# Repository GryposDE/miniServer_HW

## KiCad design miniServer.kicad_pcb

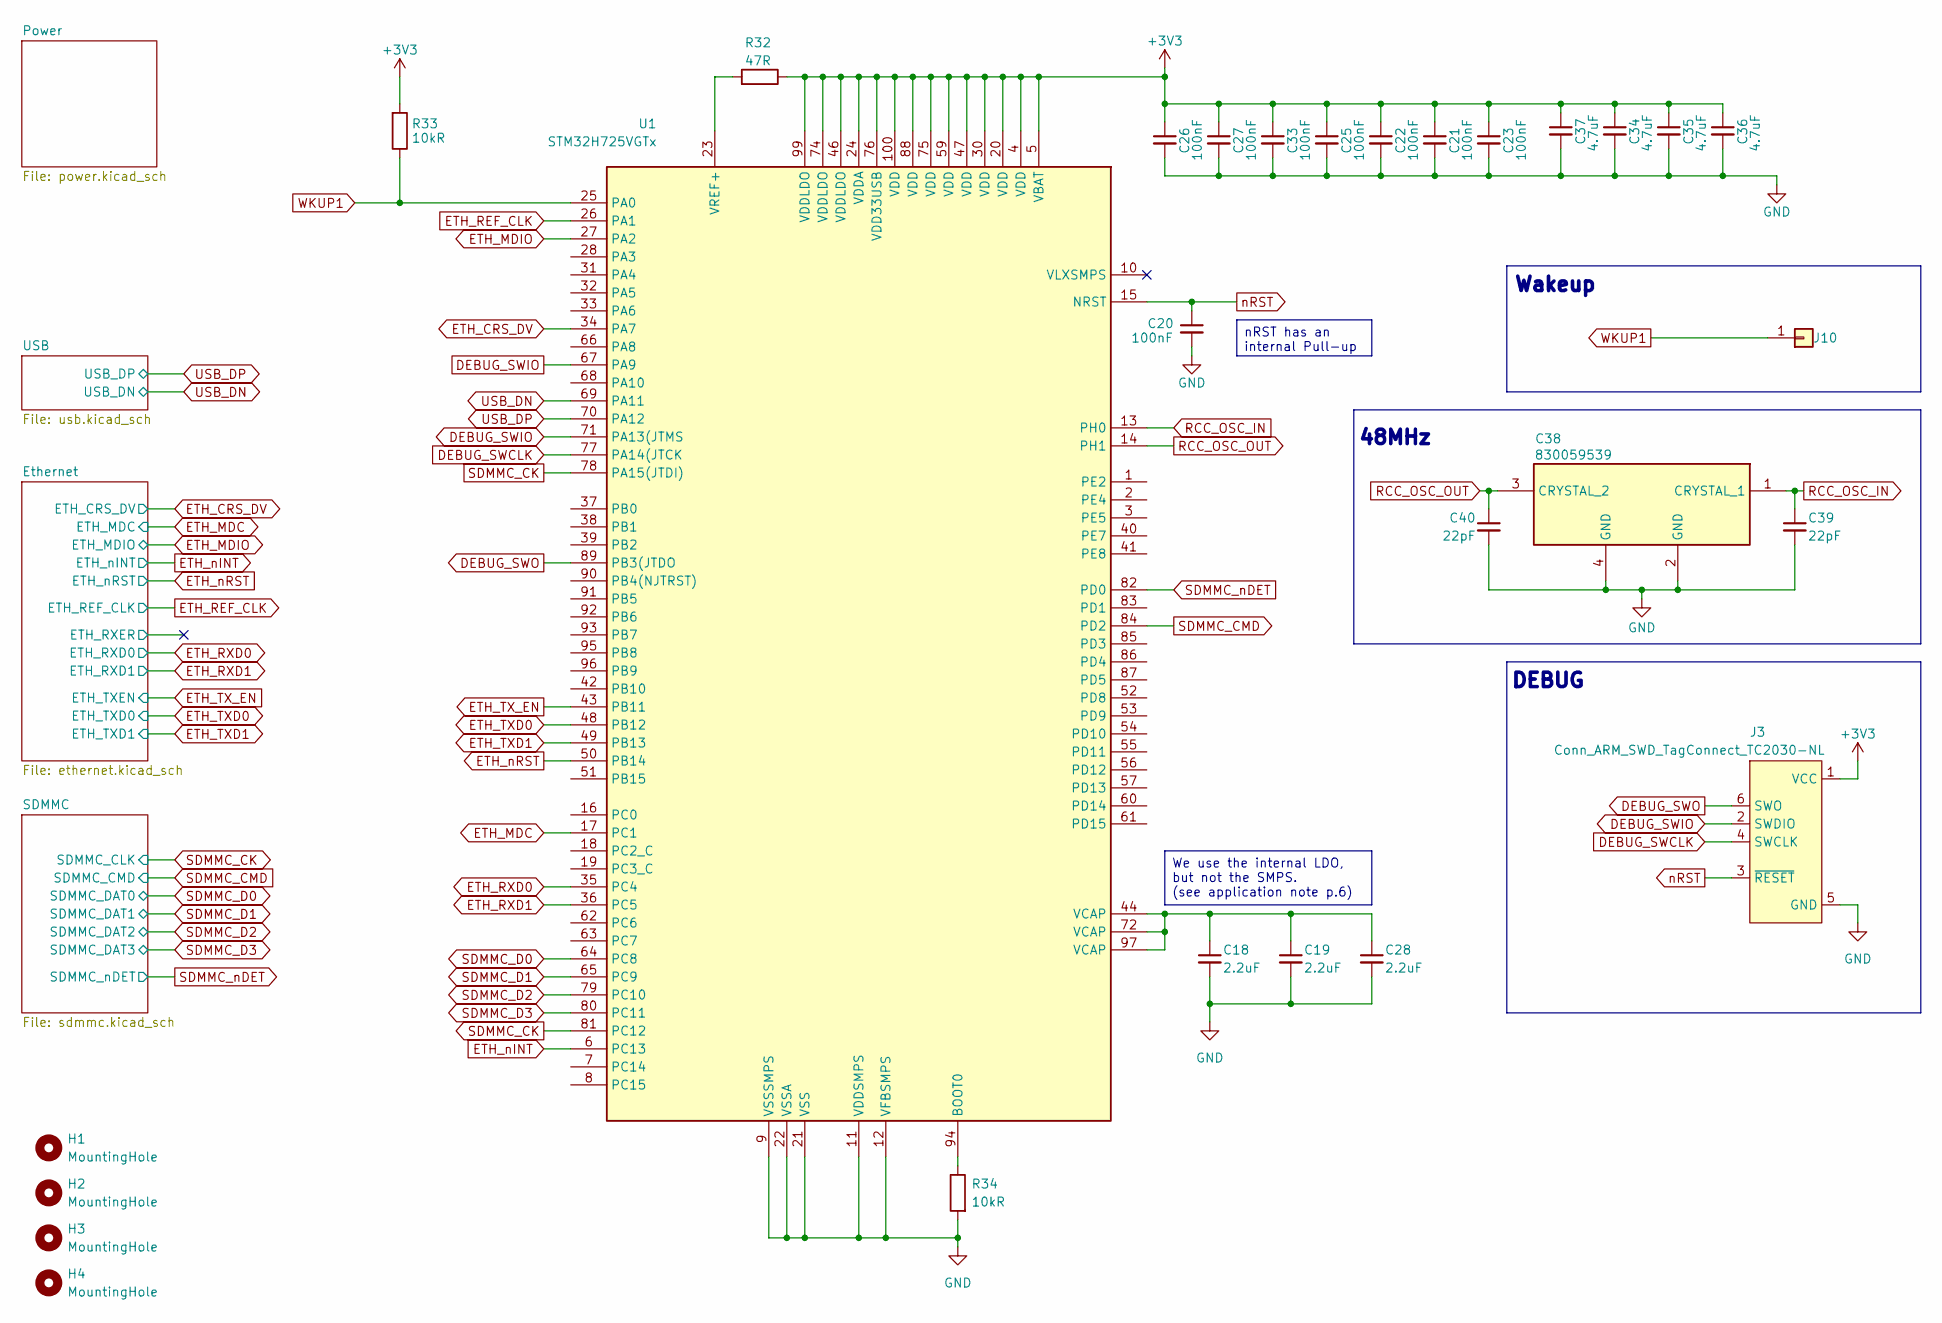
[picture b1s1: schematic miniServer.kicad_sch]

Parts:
C18, C19, C28: 2.2uF; C_0805_2012Metric_Pad1.18x1.45mm_HandSolder
C20, C21, C22, C23, C25, C26, C27, C33: 100nF; C_0805_2012Metric_Pad1.18x1.45mm_HandSolder
C34, C35, C36, C37: 4.7uF; C_0805_2012Metric_Pad1.18x1.45mm_HandSolder
C38: 830059539; Mouser Part Number 710-830059539
C39, C40: 22pF; C_0805_2012Metric_Pad1.18x1.45mm_HandSolder
H1, H2, H3, H4: MountingHole; MountingHole_2.2mm_M2
J3: Conn_ARM_SWD_TagConnect_TC2030-NL; Tag-Connect_TC2030-IDC-NL_2x03_P1.27mm_Vertical
J10: Conn_01x01; SolderWirePad_1x01_SMD_1.5x3mm
R32: 47R; R_0805_2012Metric_Pad1.20x1.40mm_HandSolder
R33, R34: 10kR; R_0805_2012Metric_Pad1.20x1.40mm_HandSolder
U1: STM32H725VGTx; LQFP-100_14x14mm_P0.5mm

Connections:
+3V3: C21.1, C22.1, C23.1, C25.1, C26.1, C27.1, C33.1, C34.1, C35.1, C36.1, C37.1, J3.1 (VCC), R32.1, R33.2, U1.4 (VDD), U1.5 (VBAT), U1.20 (VDD), U1.24 (VDDA), U1.30 (VDD), U1.46 (VDDLDO), U1.47 (VDD), U1.59 (VDD), U1.74 (VDDLDO), U1.75 (VDD), U1.76 (VDD33USB), U1.88 (VDD), U1.99 (VDDLDO), U1.100 (VDD); also elsewhere on the board
DEBUG_SWCLK: J3.4 (SWCLK), U1.77 (PA14(JTCK)
DEBUG_SWIO: J3.2 (SWDIO), U1.67 (PA9), U1.71 (PA13(JTMS)
DEBUG_SWO: J3.6 (SWO), U1.89 (PB3(JTDO)
ETH_CRS_DV: U1.34 (PA7); also elsewhere on the board
ETH_MDC: U1.17 (PC1); also elsewhere on the board
ETH_MDIO: U1.27 (PA2); also elsewhere on the board
ETH_REF_CLK: U1.26 (PA1); also elsewhere on the board
ETH_RXD0: U1.35 (PC4); also elsewhere on the board
ETH_RXD1: U1.36 (PC5); also elsewhere on the board
ETH_TXD0: U1.48 (PB12); also elsewhere on the board
ETH_TXD1: U1.49 (PB13); also elsewhere on the board
ETH_TX_EN: U1.43 (PB11); also elsewhere on the board
ETH_nINT: U1.6 (PC13); also elsewhere on the board
ETH_nRST: U1.50 (PB14); also elsewhere on the board
GND: C18.2, C19.2, C20.2, C21.2, C22.2, C23.2, C25.2, C26.2, C27.2, C28.2, C33.2, C34.2, C35.2, C36.2, C37.2, C38.2 (GND), C38.4 (GND), C39.2, C40.2, J3.5 (GND), R34.2, U1.9 (VSSSMPS), U1.11 (VDDSMPS), U1.12 (VFBSMPS), U1.21 (VSS), U1.22 (VSSA), U1.29 (VSS), U1.45 (VSS), U1.58 (VSS), U1.73 (VSS), U1.98 (VSS); also elsewhere on the board
unnamed: C18.1, C19.1, C28.1, U1.44 (VCAP), U1.72 (VCAP), U1.97 (VCAP)
unnamed: R34.1, U1.94 (BOOT0)
unnamed: R32.2, U1.23 (VREF+)
RCC_OSC_IN: C38.1 (CRYSTAL_1), C39.1, U1.13 (PH0)
RCC_OSC_OUT: C38.3 (CRYSTAL_2), C40.1, U1.14 (PH1)
SDMMC_CK: U1.78 (PA15(JTDI)), U1.81 (PC12); also elsewhere on the board
SDMMC_CMD: U1.84 (PD2); also elsewhere on the board
SDMMC_D0: U1.64 (PC8); also elsewhere on the board
SDMMC_D1: U1.65 (PC9); also elsewhere on the board
SDMMC_D2: U1.79 (PC10); also elsewhere on the board
SDMMC_D3: U1.80 (PC11); also elsewhere on the board
SDMMC_nDET: U1.82 (PD0); also elsewhere on the board
USB_DN: U1.69 (PA11); also elsewhere on the board
USB_DP: U1.70 (PA12); also elsewhere on the board
WKUP1: J10.1, R33.1, U1.25 (PA0)
nRST: C20.1, J3.3 (~RESET), U1.15 (NRST)

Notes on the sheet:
DEBUG
48MHz
Wakeup
nRST has an internal Pull-up
We use the internal LDO, but not the SMPS. (see application note p.6)

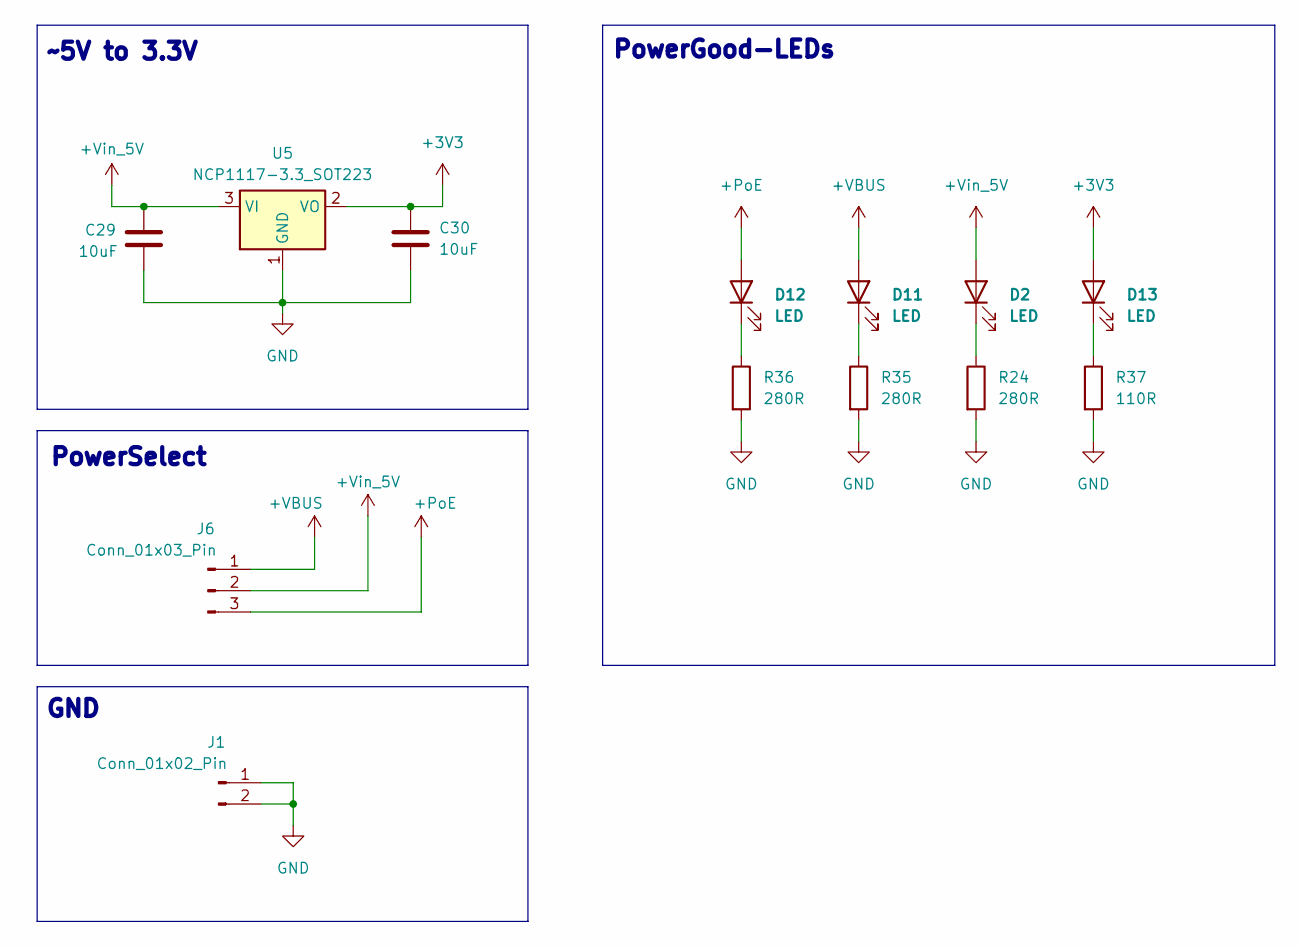
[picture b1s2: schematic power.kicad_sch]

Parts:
C29, C30: 10uF; C_0805_2012Metric_Pad1.18x1.45mm_HandSolder
D2, D11, D12, D13: LED; LED_0805_2012Metric_Pad1.15x1.40mm_HandSolder
J1: Conn_01x02_Pin; SolderWire-0.15sqmm_1x02_P4mm_D0.5mm_OD1.5mm
J6: Conn_01x03_Pin; SolderWire-0.15sqmm_1x03_P4mm_D0.5mm_OD1.5mm
R24, R35, R36: 280R; R_0805_2012Metric_Pad1.20x1.40mm_HandSolder
R37: 110R; R_0805_2012Metric_Pad1.20x1.40mm_HandSolder
U5: NCP1117-3.3_SOT223; SOT-223-3_TabPin2

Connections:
+3V3: C30.1, D13.2 (A), U5.2 (VO); also elsewhere on the board
+PoE: D12.2 (A), J6.3; also elsewhere on the board
+VBUS: D11.2 (A), J6.1; also elsewhere on the board
+Vin_5V: C29.1, D2.2 (A), J6.2, U5.3 (VI)
GND: C29.2, C30.2, J1.1, J1.2, R24.2, R35.2, R36.2, R37.2, U5.1 (GND); also elsewhere on the board
unnamed: D2.1 (K), R24.1
unnamed: D11.1 (K), R35.1
unnamed: D12.1 (K), R36.1
unnamed: D13.1 (K), R37.1

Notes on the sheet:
~5V to 3.3V
PowerSelect
PowerGood-LEDs
GND

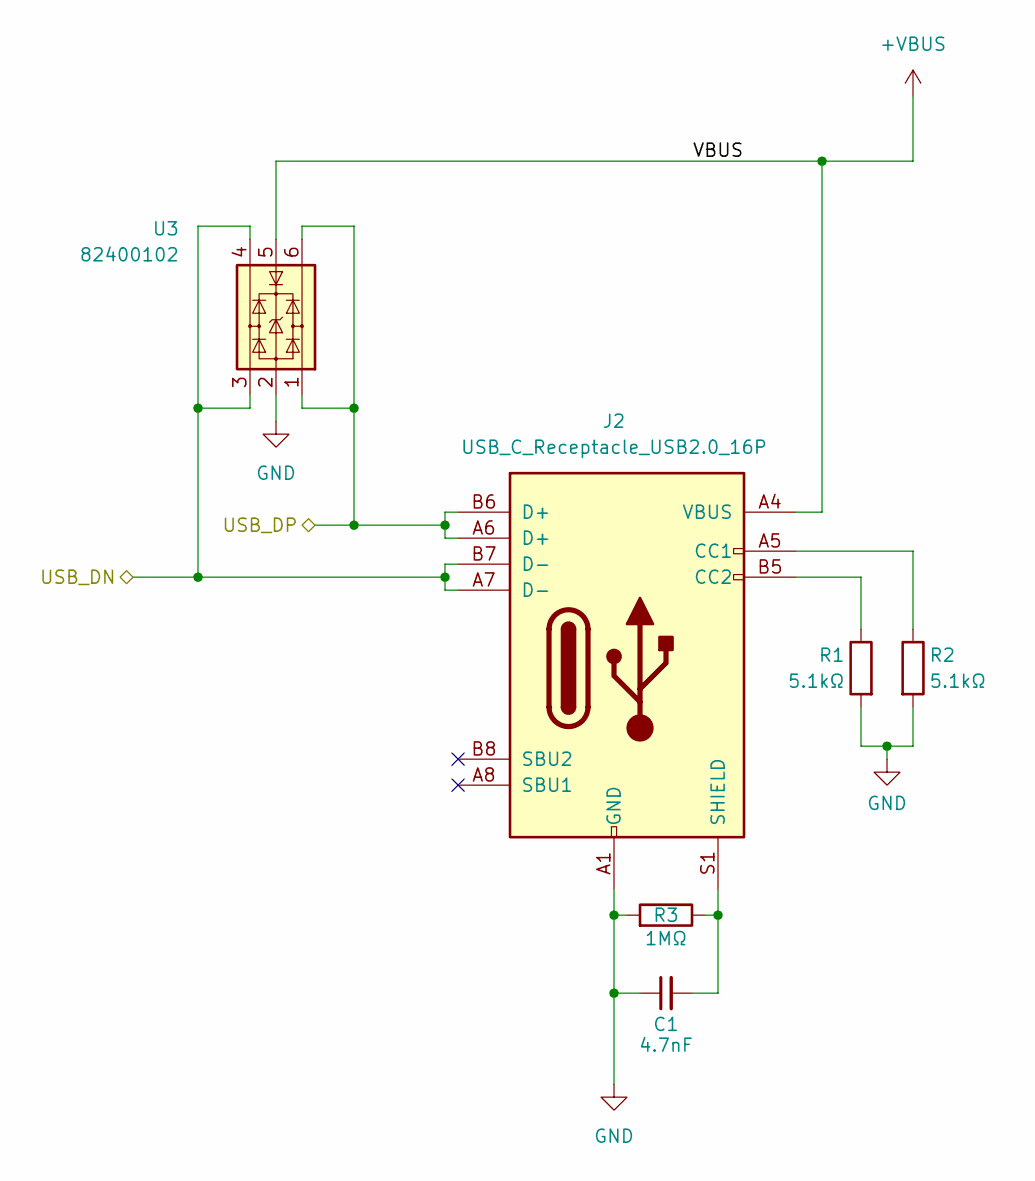
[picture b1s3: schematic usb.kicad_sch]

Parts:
C1: 4.7nF; C_0805_2012Metric_Pad1.18x1.45mm_HandSolder
J2: USB_C_Receptacle_USB2.0_16P; USB_C_Receptacle_GCT_USB4105-xx-A_16P_TopMnt_Horizontal
R1, R2: 5.1kΩ; R_0805_2012Metric_Pad1.20x1.40mm_HandSolder
R3: 1MΩ; R_0805_2012Metric_Pad1.20x1.40mm_HandSolder
U3: 82400102; SOT-23-6

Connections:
+VBUS: J2.A4 (VBUS), J2.A9 (VBUS), J2.B4 (VBUS), J2.B9 (VBUS), U3.5; also elsewhere on the board
GND: C1.1, J2.A1 (GND), J2.A12 (GND), J2.B1 (GND), J2.B12 (GND), R1.2, R2.2, R3.2, U3.2; also elsewhere on the board
unnamed: J2.A5 (CC1), R2.1
unnamed: J2.B5 (CC2), R1.1
unnamed: C1.2, J2.S1 (SHIELD), R3.1
USB_DN: J2.A7 (D-), J2.B7 (D-), U3.3, U3.4; also elsewhere on the board
USB_DP: J2.A6 (D+), J2.B6 (D+), U3.1, U3.6; also elsewhere on the board

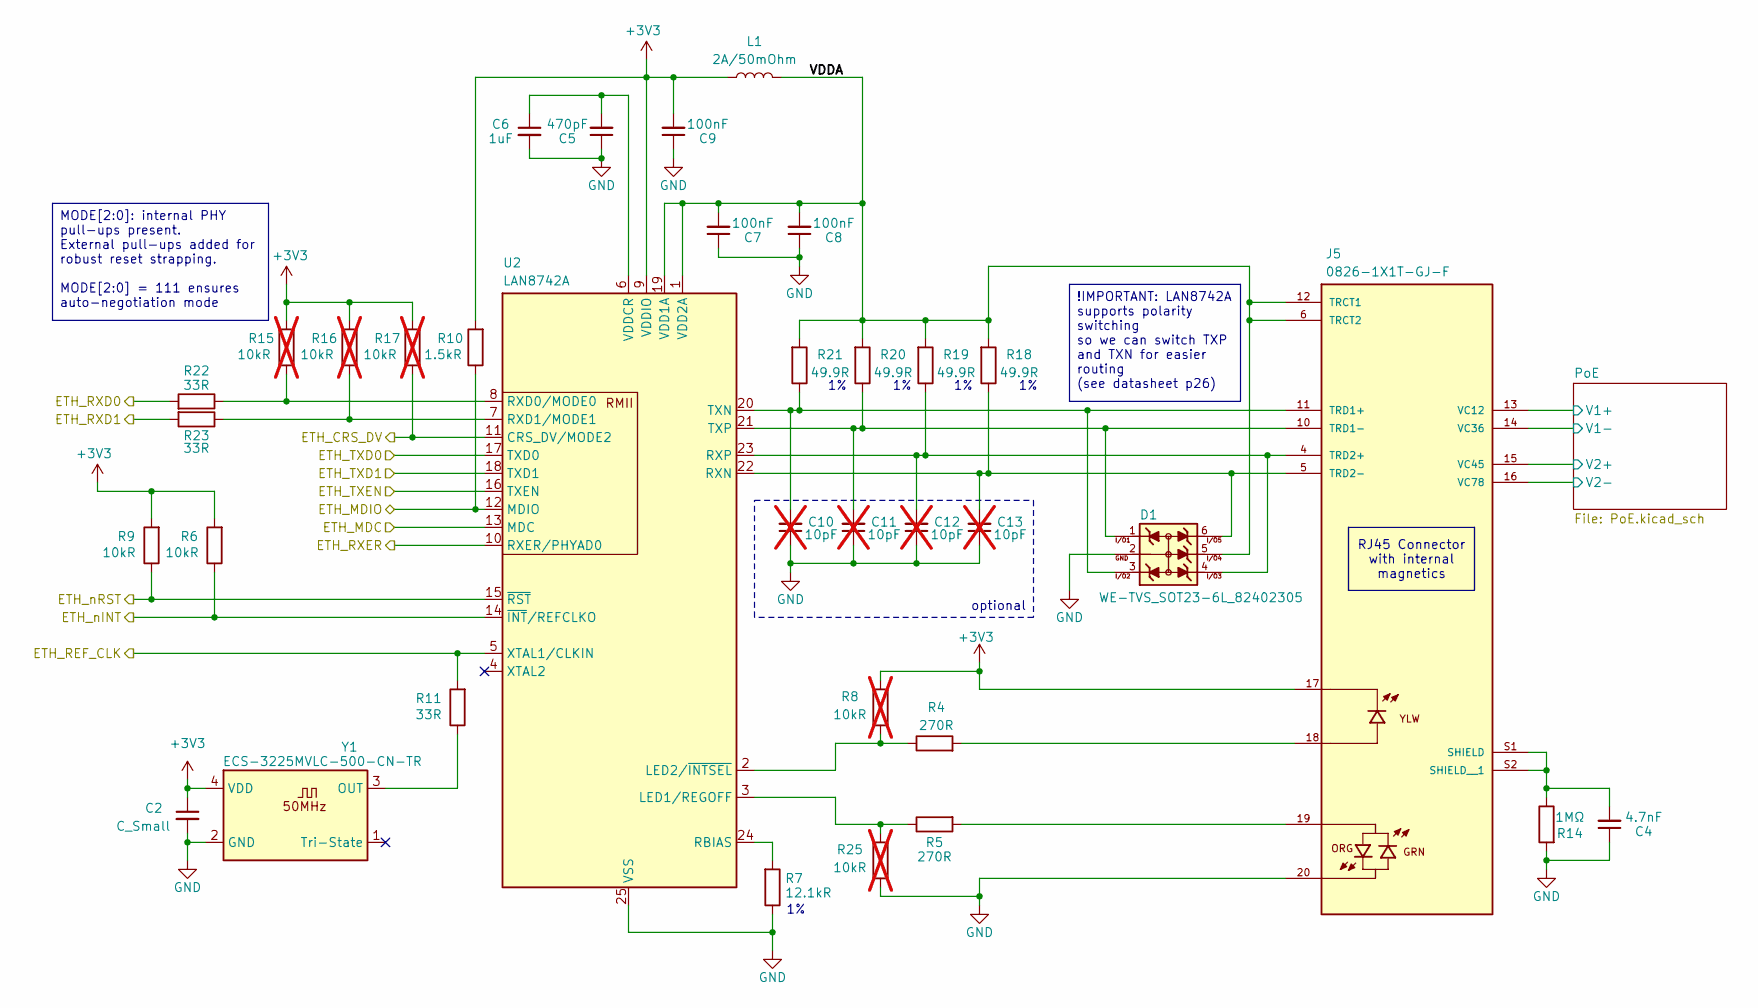
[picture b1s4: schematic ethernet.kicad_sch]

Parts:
C2: C_Small; C_0805_2012Metric_Pad1.18x1.45mm_HandSolder
C4: 4.7nF; C_0805_2012Metric_Pad1.18x1.45mm_HandSolder
C5: 470pF; C_0805_2012Metric_Pad1.18x1.45mm_HandSolder
C6: 1uF; C_0805_2012Metric_Pad1.18x1.45mm_HandSolder
C7, C8, C9: 100nF; C_0805_2012Metric_Pad1.18x1.45mm_HandSolder
C10, C11, C12, C13: 10pF; C_0805_2012Metric_Pad1.18x1.45mm_HandSolder; not fitted
D1: WE-TVS_SOT23-6L_82402305; WE-TVS_SOT23-6L
J5: 0826-1X1T-GJ-F; BEL_0826-1X1T-GJ-F; PARTREV D
L1: 2A/50mOhm; L_0805_2012Metric_Pad1.05x1.20mm_HandSolder
R4, R5: 270R; R_0805_2012Metric_Pad1.20x1.40mm_HandSolder
R6, R9: 10kR; R_0805_2012Metric_Pad1.20x1.40mm_HandSolder
R7: 12.1kR; R_0805_2012Metric_Pad1.20x1.40mm_HandSolder
R8, R15, R16, R17, R25: 10kR; R_0805_2012Metric_Pad1.20x1.40mm_HandSolder; not fitted
R10: 1.5kR; R_0805_2012Metric_Pad1.20x1.40mm_HandSolder
R11, R22, R23: 33R; R_0805_2012Metric_Pad1.20x1.40mm_HandSolder
R14: 1MΩ; R_0805_2012Metric_Pad1.20x1.40mm_HandSolder
R18, R19, R20, R21: 49.9R; R_0805_2012Metric_Pad1.20x1.40mm_HandSolder
U2: LAN8742A; VQFN-24-1EP_4x4mm_P0.5mm_EP2.5x2.5mm_ThermalVias
Y1: ECS-3225MVLC-500-CN-TR; Oscillator_SMD_ECS_2520MV-xxx-xx-4Pin_2.5x2.0mm

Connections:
+3V3: C2.1, C9.2, J5.17, L1.1, R6.2, R8.2, R9.2, R10.2, R15.2, R16.2, R17.2, U2.9 (VDDIO), Y1.4 (VDD); also elsewhere on the board
/Ethernet/ETH_RXER: U2.10 (RXER/PHYAD0)
/Ethernet/PoE/V1+: J5.13 (VC12); also elsewhere on the board
/Ethernet/PoE/V1-: J5.14 (VC36); also elsewhere on the board
/Ethernet/PoE/V2+: J5.15 (VC45); also elsewhere on the board
/Ethernet/PoE/V2-: J5.16 (VC78); also elsewhere on the board
/Ethernet/VDDA: C7.2, C8.2, D1.5, J5.6 (TRCT2), J5.12 (TRCT1), L1.2, R18.2, R19.2, R20.2, R21.2, U2.1 (VDD2A), U2.19 (VDD1A)
ETH_CRS_DV: R17.1, U2.11 (CRS_DV/MODE2); also elsewhere on the board
ETH_MDC: U2.13 (MDC); also elsewhere on the board
ETH_MDIO: R10.1, U2.12 (MDIO); also elsewhere on the board
ETH_REF_CLK: R11.2, U2.5 (XTAL1/CLKIN); also elsewhere on the board
ETH_RXD0: R22.2; also elsewhere on the board
ETH_RXD1: R23.2; also elsewhere on the board
ETH_TXD0: U2.17 (TXD0); also elsewhere on the board
ETH_TXD1: U2.18 (TXD1); also elsewhere on the board
ETH_TX_EN: U2.16 (TXEN); also elsewhere on the board
ETH_nINT: R6.1, U2.14 (~INT/REFCLKO); also elsewhere on the board
ETH_nRST: R9.1, U2.15 (~RST); also elsewhere on the board
GND: C2.2, C4.1, C5.1, C6.2, C7.1, C8.1, C9.1, C10.1, C11.1, C12.1, C13.1, D1.2, J5.20, R7.1, R14.2, R25.1, U2.25 (VSS), Y1.2 (GND); also elsewhere on the board
unnamed: J5.18, R4.2
unnamed: J5.19, R5.2
unnamed: C4.2, J5.S1 (SHIELD), J5.S2 (SHIELD__1), R14.1
unnamed: C10.2, D1.3, J5.11 (TRD1+), R21.1, U2.20 (TXN)
unnamed: C11.2, D1.1, J5.10 (TRD1-), R20.1, U2.21 (TXP)
unnamed: C12.2, D1.4, J5.4 (TRD2+), R19.1, U2.23 (RXP)
unnamed: C13.2, D1.6, J5.5 (TRD2-), R18.1, U2.22 (RXN)
unnamed: R5.1, R25.2, U2.3 (LED1/REGOFF)
unnamed: R4.1, R8.1, U2.2 (LED2/~INTSEL)
unnamed: R7.2, U2.24 (RBIAS)
unnamed: R15.1, R22.1, U2.8 (RXD0/MODE0)
unnamed: R16.1, R23.1, U2.7 (RXD1/MODE1)
unnamed: C5.2, C6.1, U2.6 (VDDCR)
unnamed: R11.1, Y1.3 (OUT)

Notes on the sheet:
RJ45 Connector with internal magnetics
!IMPORTANT: LAN8742A supports polarity switching so we can switch TXP and TXN for easier routing (see datasheet p26)
MODE[2:0]: internal PHY pull-ups present. External pull-ups added for robust reset strapping. MODE[2:0] = 111 ensures auto-negotiation mode
optional

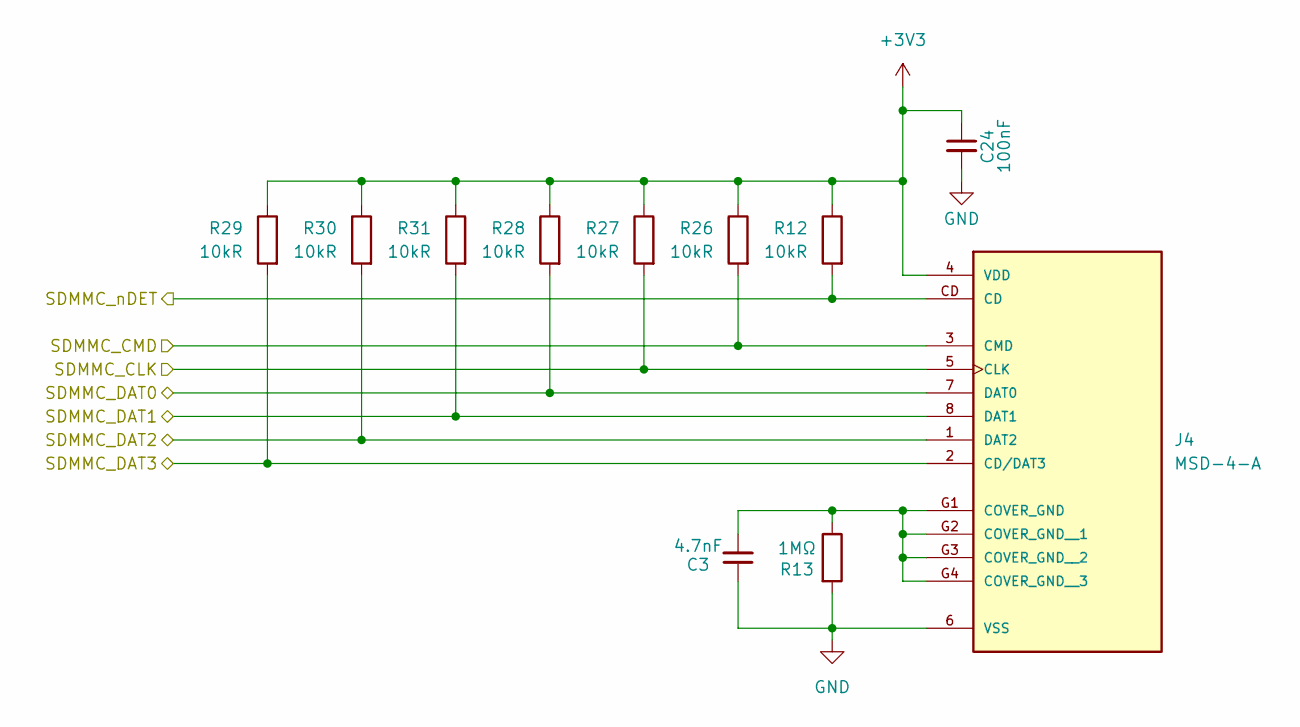
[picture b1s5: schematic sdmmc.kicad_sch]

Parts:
C3: 4.7nF; C_0805_2012Metric_Pad1.18x1.45mm_HandSolder
C24: 100nF; C_0805_2012Metric_Pad1.18x1.45mm_HandSolder
J4: MSD-4-A; CUI_MSD-4-A; PARTREV 1.0
R12, R26, R27, R28, R29, R30, R31: 10kR; R_0805_2012Metric_Pad1.20x1.40mm_HandSolder
R13: 1MΩ; R_0805_2012Metric_Pad1.20x1.40mm_HandSolder

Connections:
+3V3: C24.1, J4.4 (VDD), R12.1, R26.1, R27.1, R28.1, R29.1, R30.1, R31.1; also elsewhere on the board
GND: C3.1, C24.2, J4.6 (VSS), R13.2; also elsewhere on the board
unnamed: C3.2, J4.G1 (COVER_GND), J4.G2 (COVER_GND__1), J4.G3 (COVER_GND__2), J4.G4 (COVER_GND__3), R13.1
SDMMC_CK: J4.5 (CLK), R27.2; also elsewhere on the board
SDMMC_CMD: J4.3 (CMD), R26.2; also elsewhere on the board
SDMMC_D0: J4.7 (DAT0), R28.2; also elsewhere on the board
SDMMC_D1: J4.8 (DAT1), R31.2; also elsewhere on the board
SDMMC_D2: J4.1 (DAT2), R30.2; also elsewhere on the board
SDMMC_D3: J4.2 (CD/DAT3), R29.2; also elsewhere on the board
SDMMC_nDET: J4.CD, R12.2; also elsewhere on the board

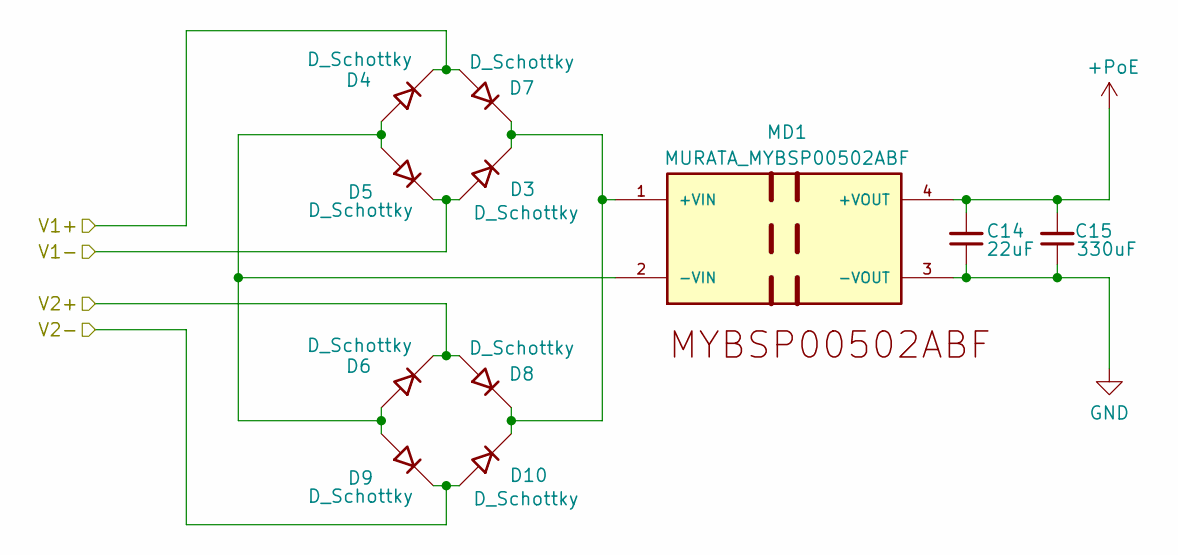
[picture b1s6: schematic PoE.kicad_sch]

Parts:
C14: 22uF; C_0805_2012Metric_Pad1.18x1.45mm_HandSolder
C15: 330uF; C_0805_2012Metric_Pad1.18x1.45mm_HandSolder
D3, D4, D5, D6, D7, D8, D9, D10: D_Schottky; Nexperia_CFP3_SOD-123W
MD1: MURATA_MYBSP00502ABF; MURATA_MYBSP00502ABF_0

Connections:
+PoE: C14.2, C15.2, MD1.4 (+VOUT); also elsewhere on the board
/Ethernet/PoE/V1+: D4.1 (K), D7.2 (A); also elsewhere on the board
/Ethernet/PoE/V1-: D3.2 (A), D5.1 (K); also elsewhere on the board
/Ethernet/PoE/V2+: D6.1 (K), D8.2 (A); also elsewhere on the board
/Ethernet/PoE/V2-: D9.1 (K), D10.2 (A); also elsewhere on the board
GND: C14.1, C15.1, MD1.3 (-VOUT); also elsewhere on the board
unnamed: D4.2 (A), D5.2 (A), D6.2 (A), D9.2 (A), MD1.2 (-VIN)
unnamed: D3.1 (K), D7.1 (K), D8.1 (K), D10.1 (K), MD1.1 (+VIN)

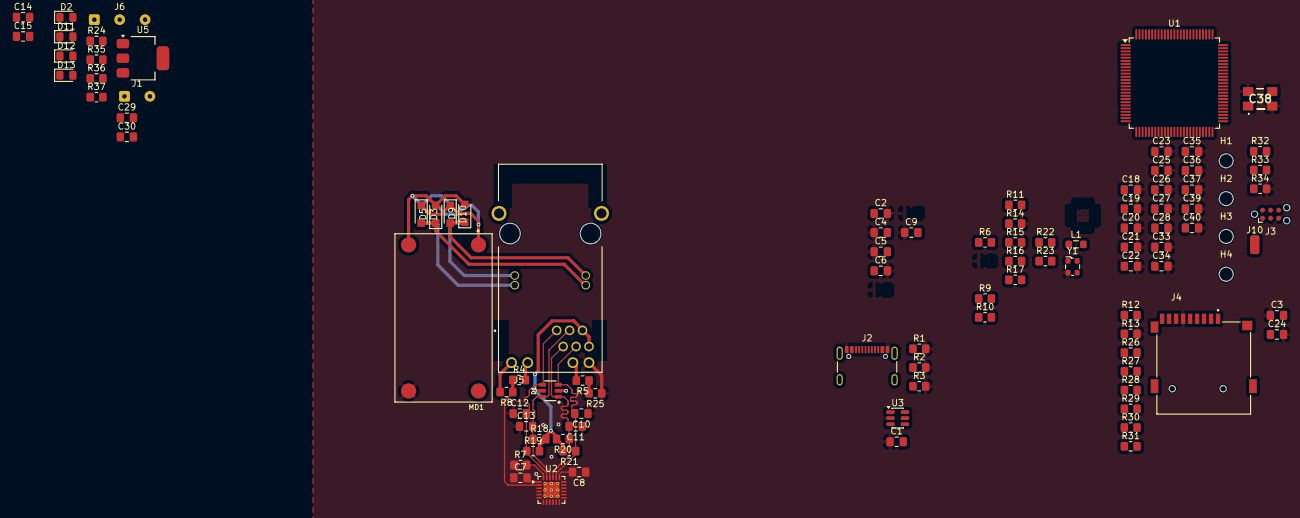
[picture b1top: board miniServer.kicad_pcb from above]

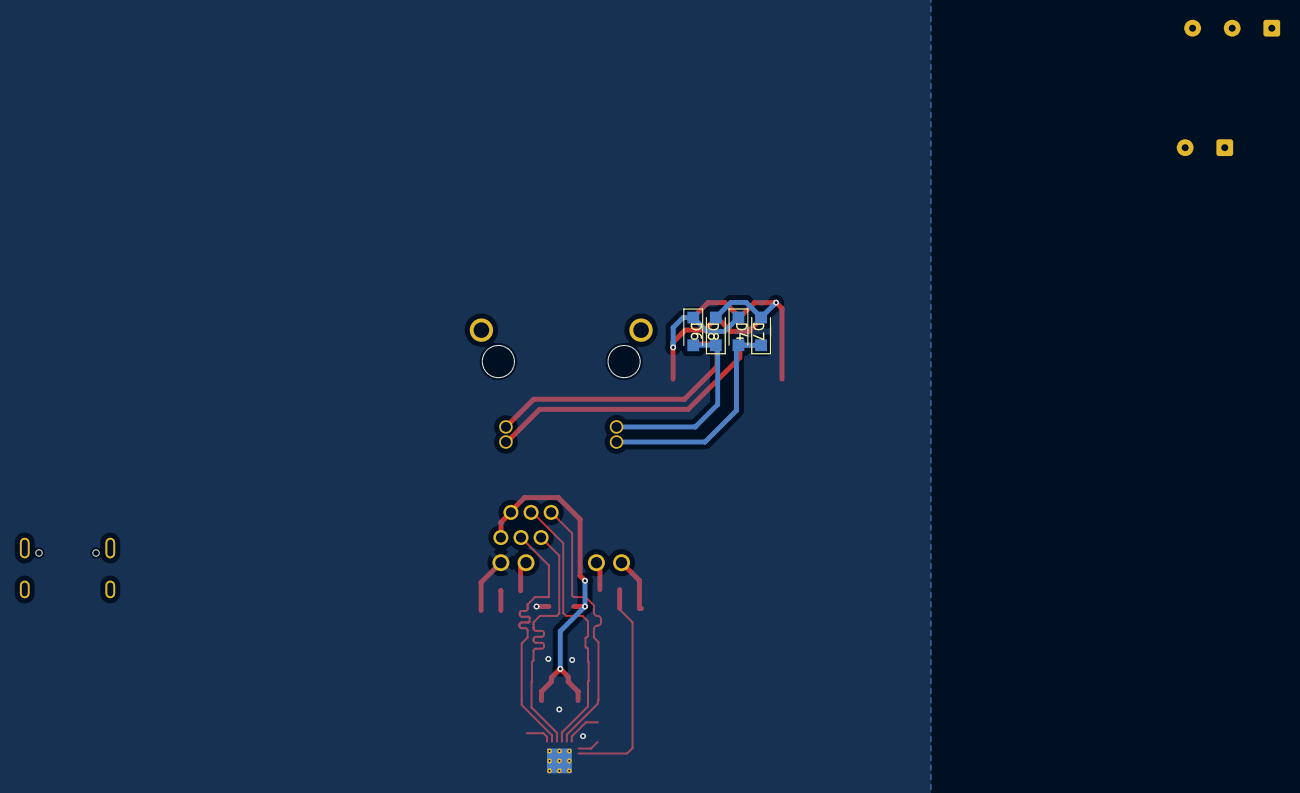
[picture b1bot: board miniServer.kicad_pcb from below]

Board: 4 copper layers, 104 parts (4 on the bottom side), 64 nets.

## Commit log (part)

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2026-04-19 Started with USB + VBUS power supply
2026-04-20 Worked on ETH
2026-06-07 Added SDMMC
2026-06-14 Placed some components on PCB layout
2026-06-14 Worked on ETH PHY schematic
2026-06-14 improved ETH schematics
